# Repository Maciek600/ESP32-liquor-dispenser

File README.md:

# ESP32 Alcohol Dispenser with Scale
### The goal of the project was to create a beverage dispenser with a built-in scale that precisely controls the amount of liquid poured. The device automatically dispenses the user-specified amount of liquid, measured based on the weight of the cup or glass. The user places a glass on a base with an integrated scale (load cell). When the distance sensor detects the presence of a glass, the scale resets, and the user selects the desired amount of beverage using a control panel with buttons. After confirmation, the device automatically starts pouring, continuously monitoring the weight and precisely stopping the dispensing once the selected amount is reached. If no container is detected or the limit is reached, the system displays an appropriate message.

### The schematic and design were created using Autodesk Eagle. The code was written using Arduino IDE.

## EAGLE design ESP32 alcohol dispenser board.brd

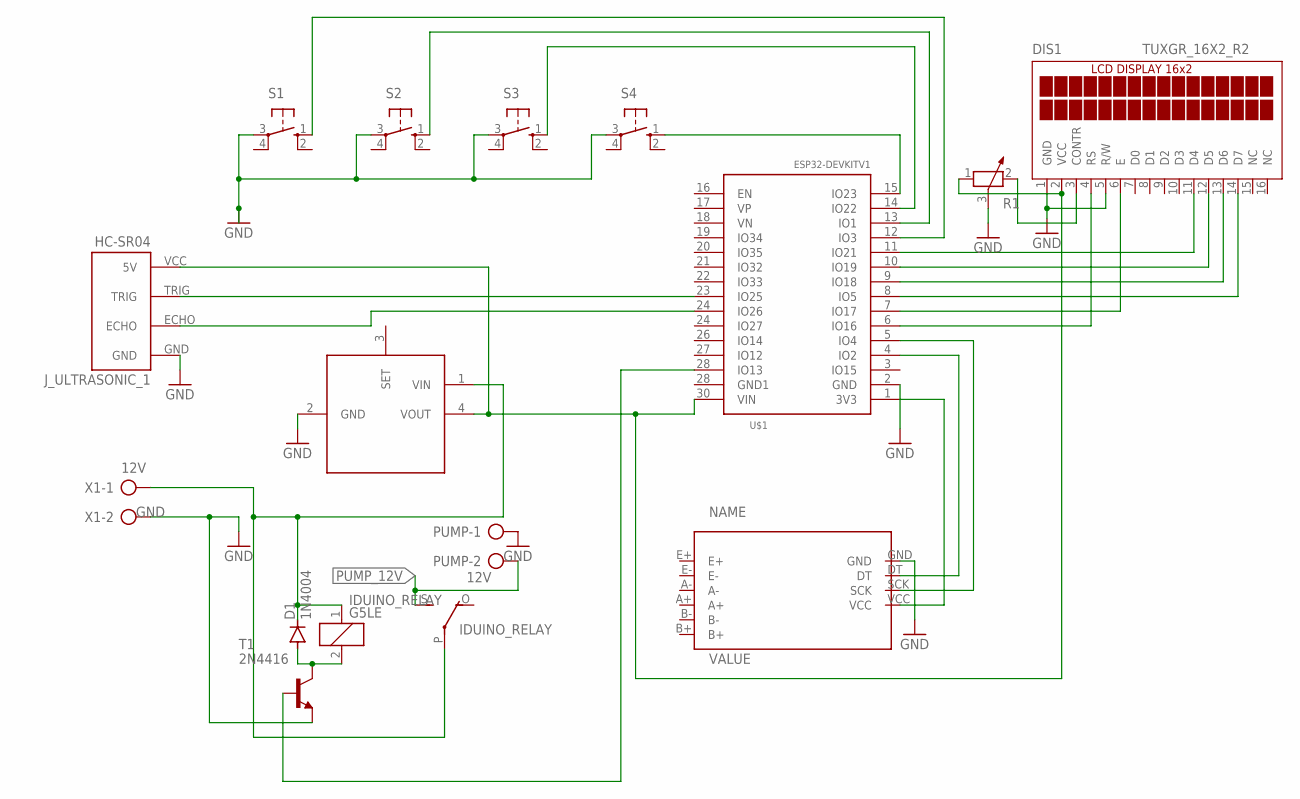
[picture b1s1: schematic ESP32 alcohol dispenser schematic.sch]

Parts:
D1: 1N4004; DO41-10
DIS1: TUXGR_16X2_R2
IDUINO_RELAY: G5LE
J_ULTRASONIC_1: HC-SR04; HC-SR04_FOOTPRINT
LM25965: LM2596S_MODULE; MOLEX-1X4_LOCK
PUMP: 12V; AK500/2-H
R1: POTENTIOMETER_PT-10; PT-10
S1, S2, S3, S4: 10-XX; B3F-10XX
T1: 2N4416; TO92
U$1: ESP32DEVKITV1; ESP32-DEVKITV1
U$3: HX711A; HX711
X1: AK300/2

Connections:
GND: DIS1.1 (GND), DIS1.5 (R/W), J_ULTRASONIC_1.GND, LM25965.2 (GND), PUMP.1, R1.3, S1.3, S2.3, S3.3, S4.3, T1.3 (E), U$1.2 (GND), U$3.GND, X1.2
unnamed: DIS1.6 (E), U$1.7 (IO17)
unnamed: T1.2 (B), U$1.28 (IO13)
unnamed: U$1.1 (3V3), U$3.VCC
unnamed: U$1.4 (IO2), U$3.DT
unnamed: U$1.5 (IO4), U$3.SCK
unnamed: J_ULTRASONIC_1.ECHO, U$1.24 (IO27)
unnamed: J_ULTRASONIC_1.TRIG, U$1.23 (IO25)
unnamed: S4.1 (S), U$1.15 (IO23)
unnamed: S3.1 (S), U$1.14 (IO22)
unnamed: S2.1 (S), U$1.13 (IO1)
unnamed: S1.1 (S), U$1.12 (IO3)
unnamed: D1.A, IDUINO_RELAY.2, T1.1 (C)
unnamed: DIS1.11 (D4), U$1.11 (IO21)
unnamed: DIS1.12 (D5), U$1.10 (IO19)
unnamed: DIS1.13 (D6), U$1.9 (IO18)
unnamed: DIS1.14 (D7), U$1.8 (IO5)
unnamed: DIS1.2 (VCC), J_ULTRASONIC_1.VCC (5V), LM25965.4 (VOUT), R1.1, U$1.30 (VIN)
unnamed: DIS1.4 (RS), U$1.6 (IO16)
unnamed: D1.C, IDUINO_RELAY.1, IDUINO_RELAY.P, LM25965.1 (VIN), X1.1
unnamed: DIS1.3 (CONTR), R1.2
PUMP_12V: IDUINO_RELAY.S, PUMP.2

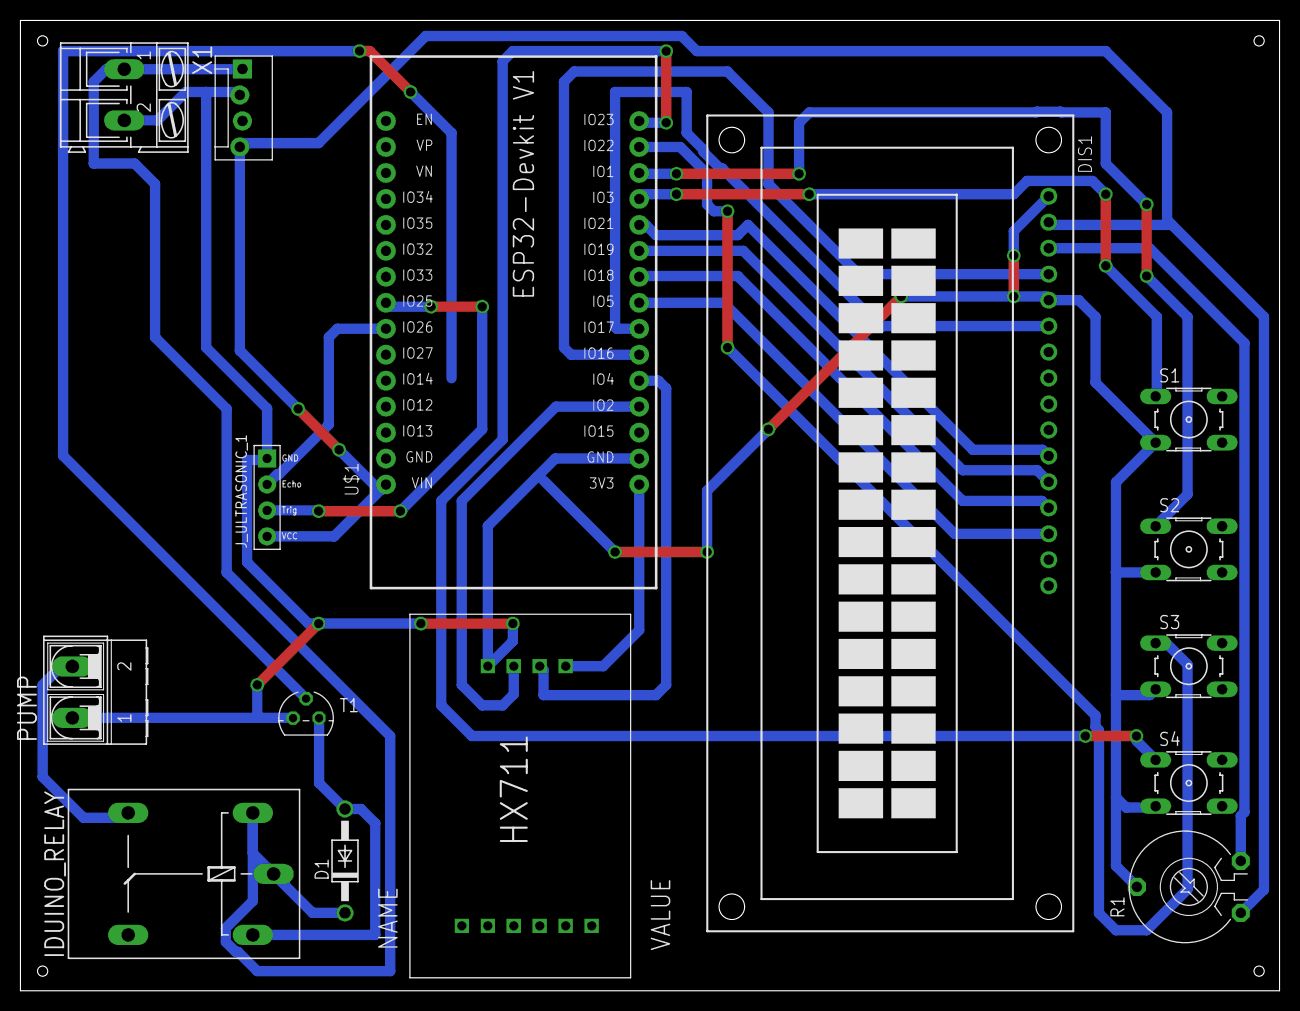
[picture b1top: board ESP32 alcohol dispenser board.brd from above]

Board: 2 copper layers, 123.2 x 94.9 mm, 15 parts (0 on the bottom side), 22 nets.
